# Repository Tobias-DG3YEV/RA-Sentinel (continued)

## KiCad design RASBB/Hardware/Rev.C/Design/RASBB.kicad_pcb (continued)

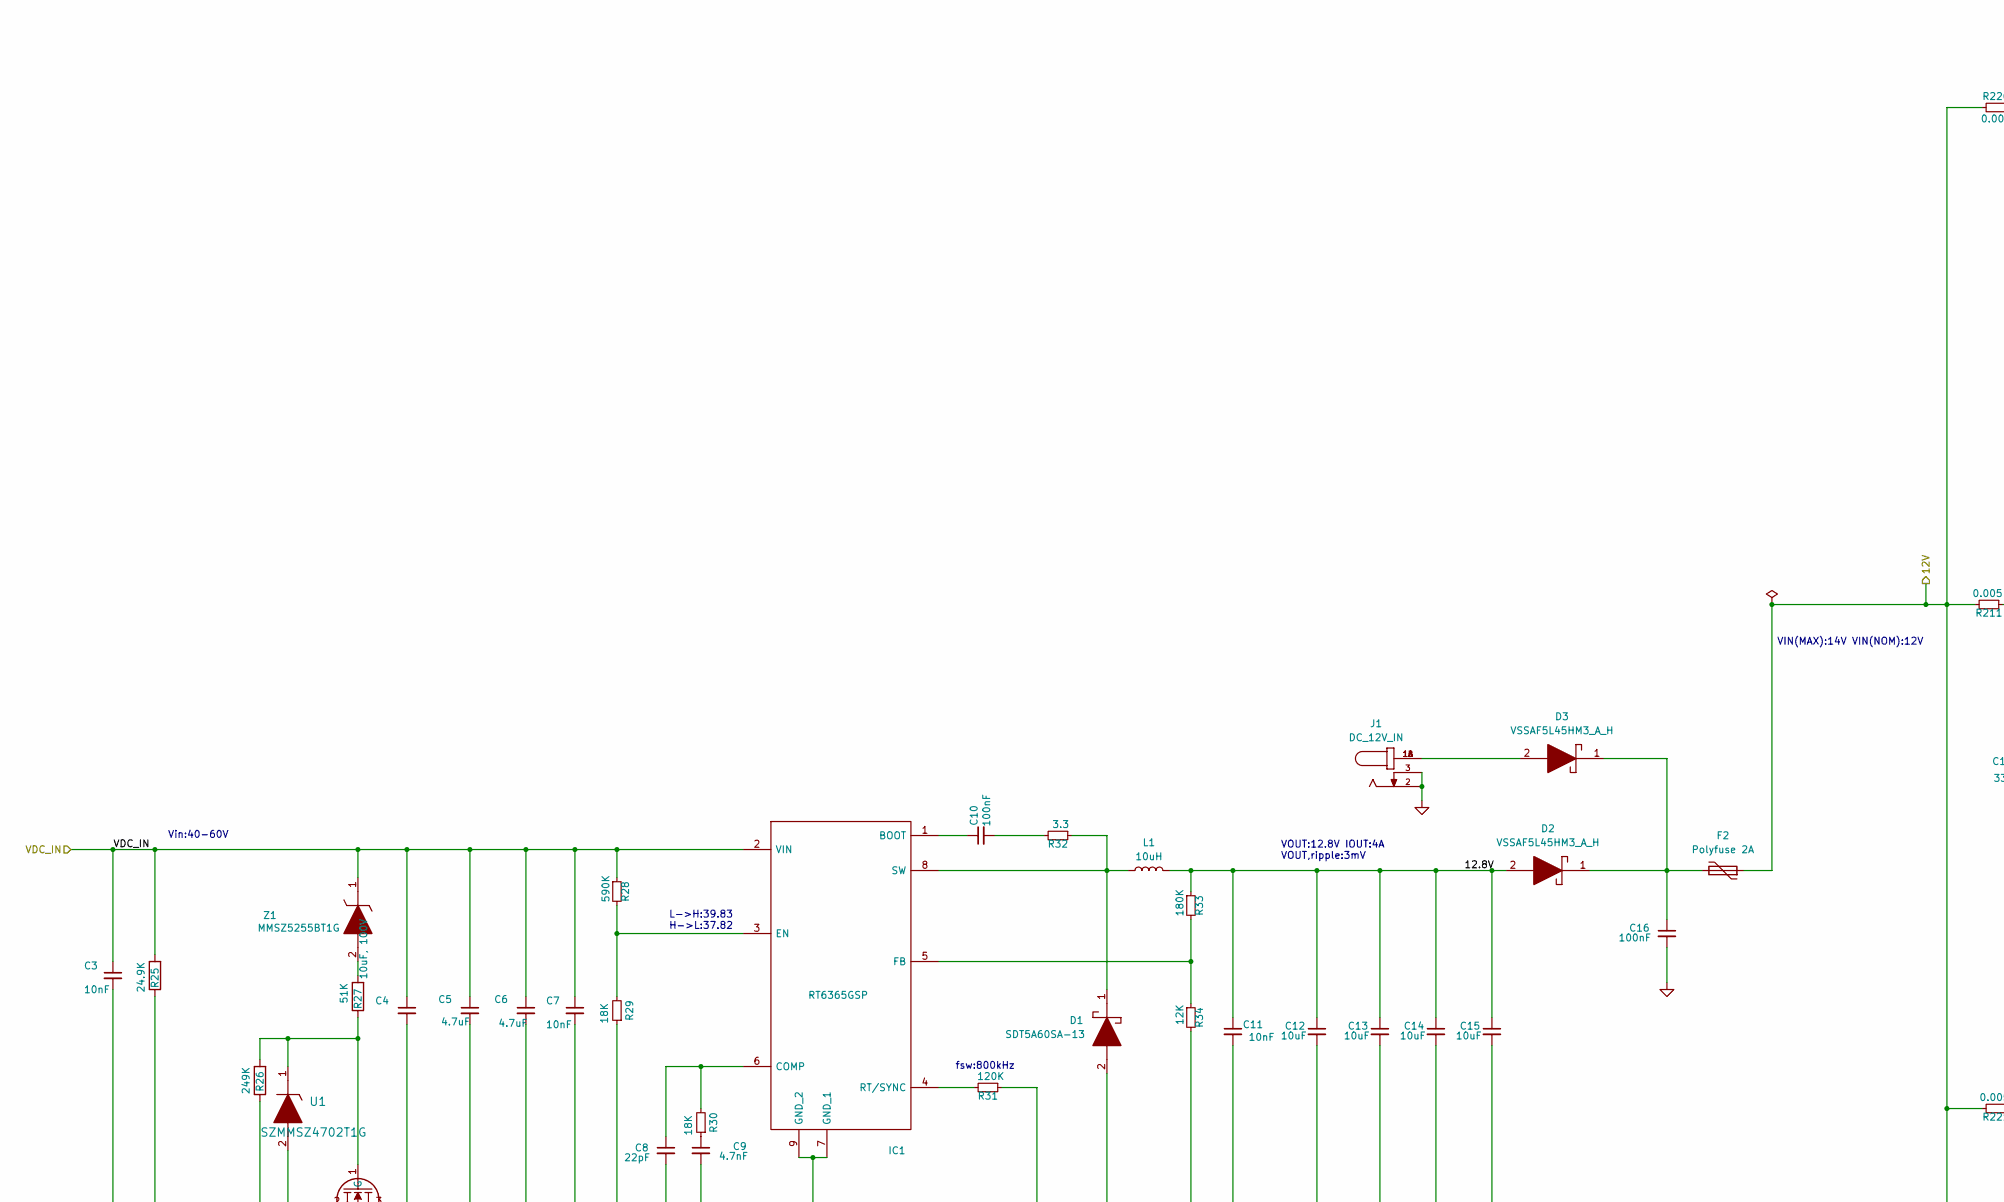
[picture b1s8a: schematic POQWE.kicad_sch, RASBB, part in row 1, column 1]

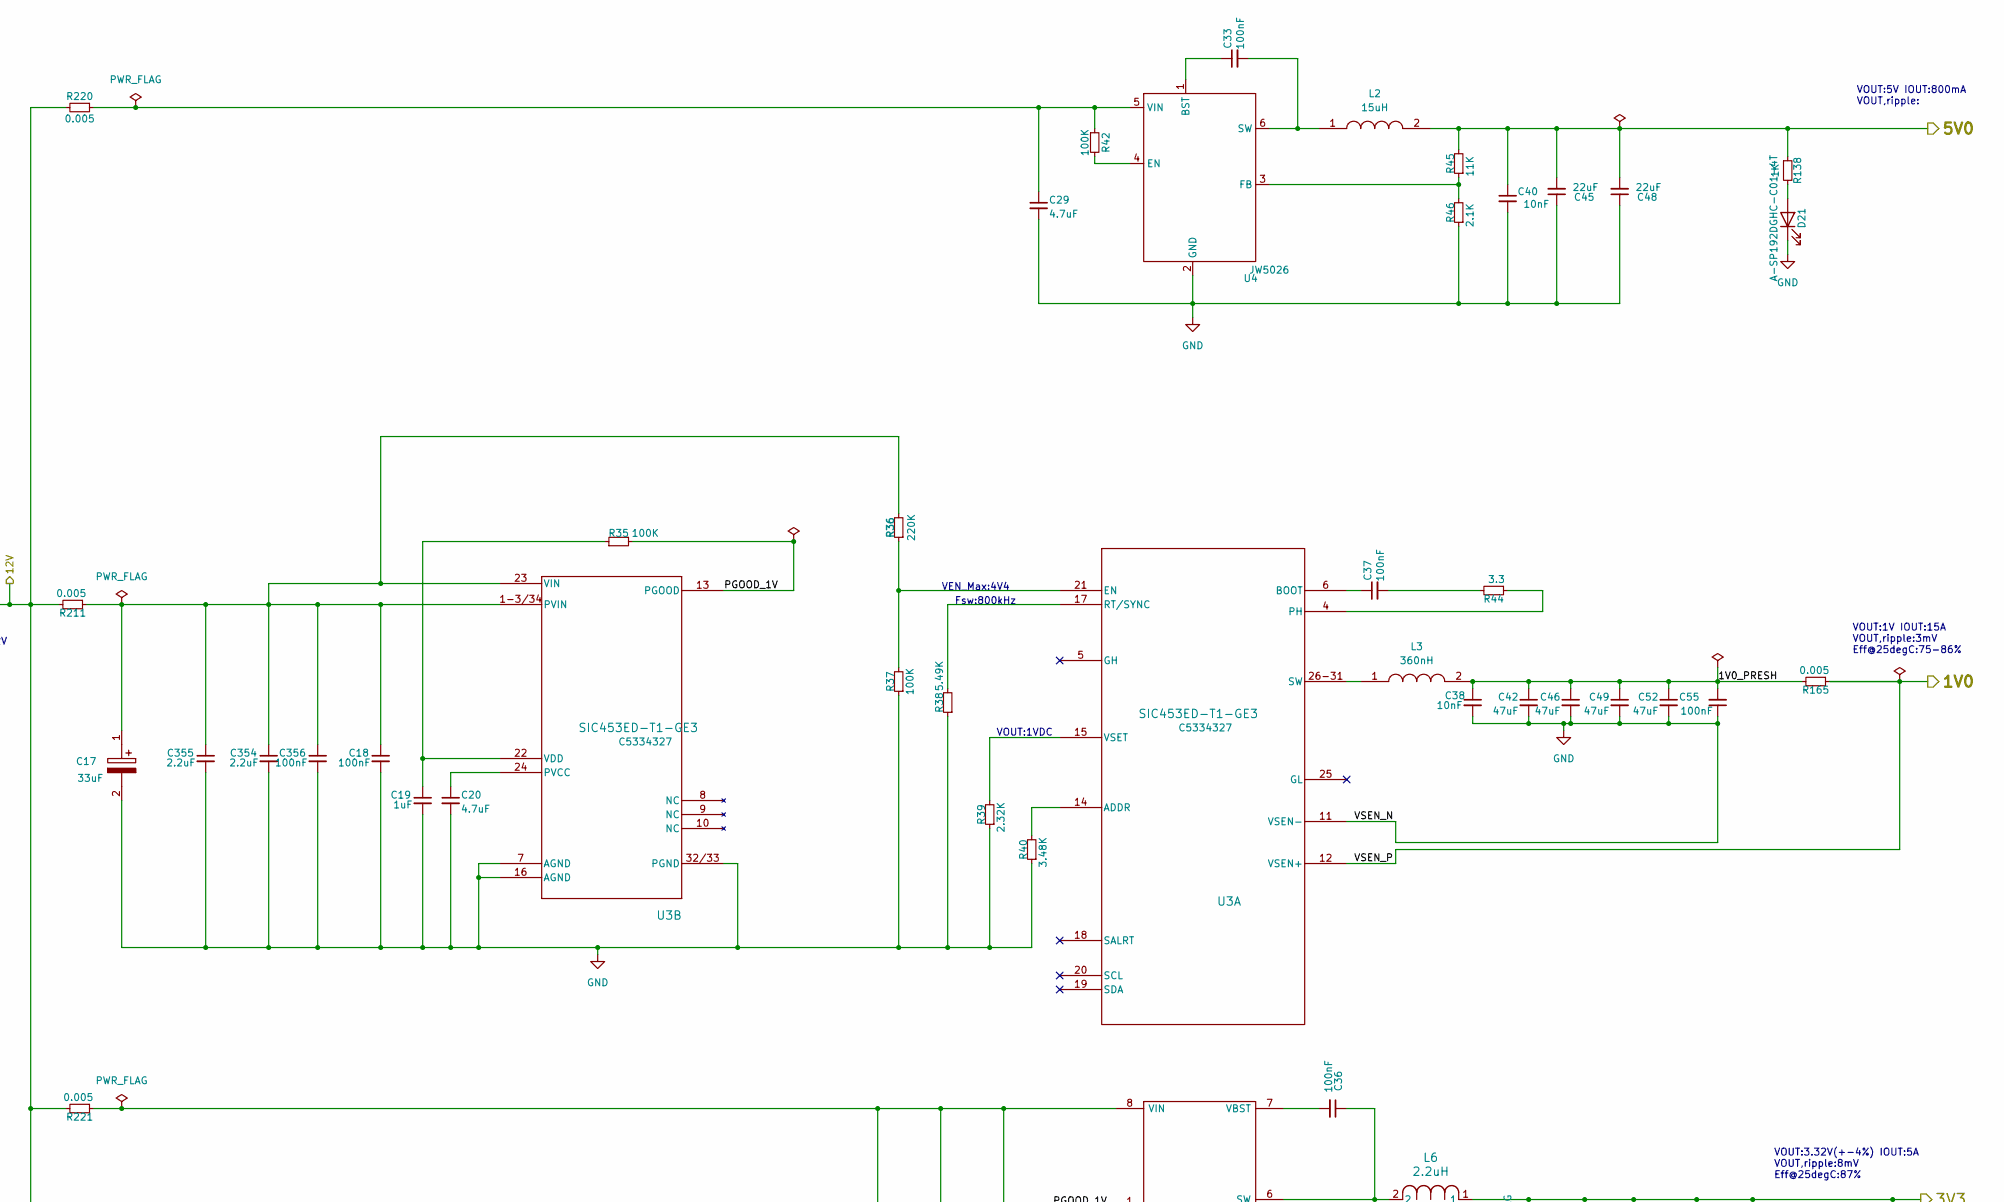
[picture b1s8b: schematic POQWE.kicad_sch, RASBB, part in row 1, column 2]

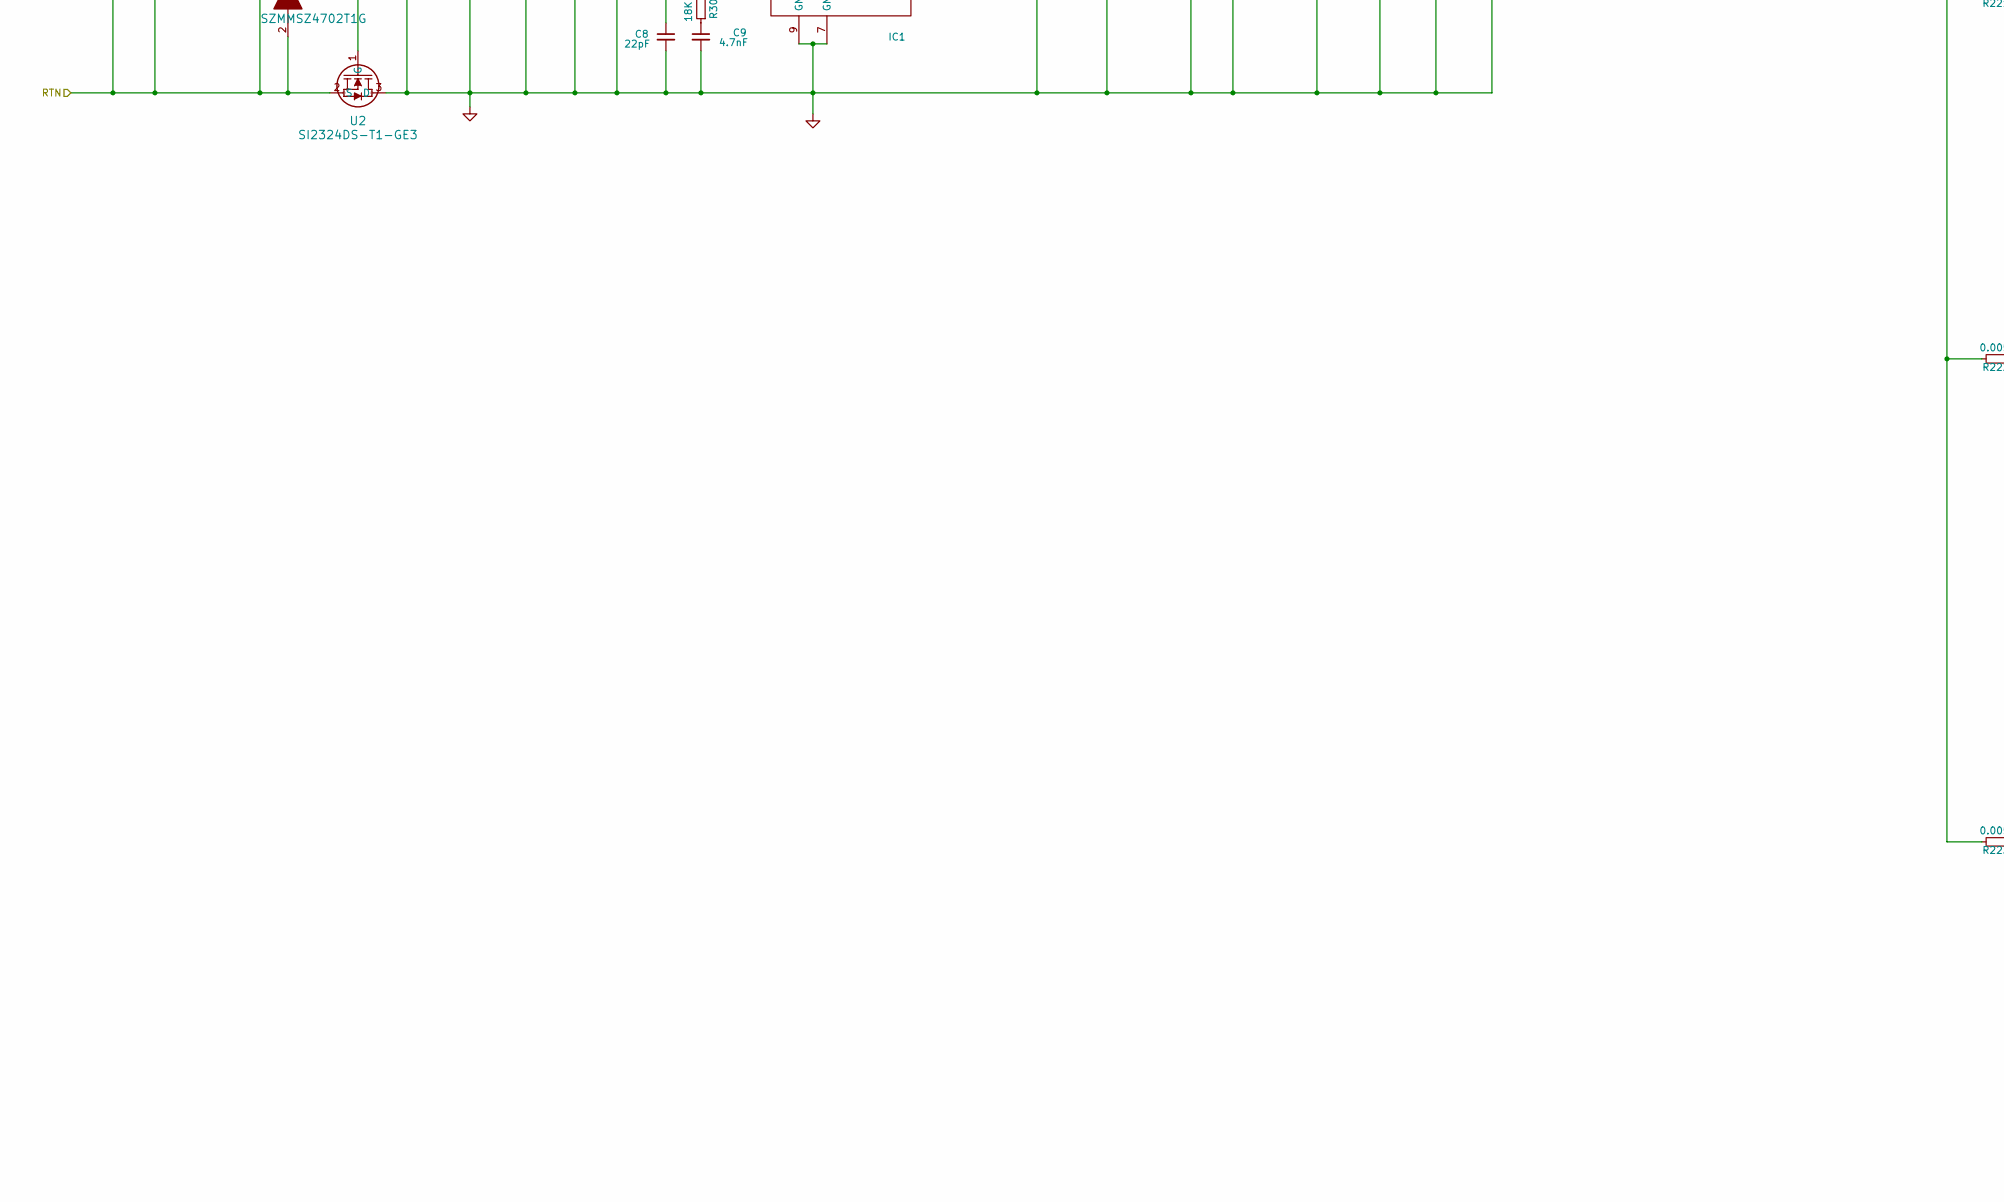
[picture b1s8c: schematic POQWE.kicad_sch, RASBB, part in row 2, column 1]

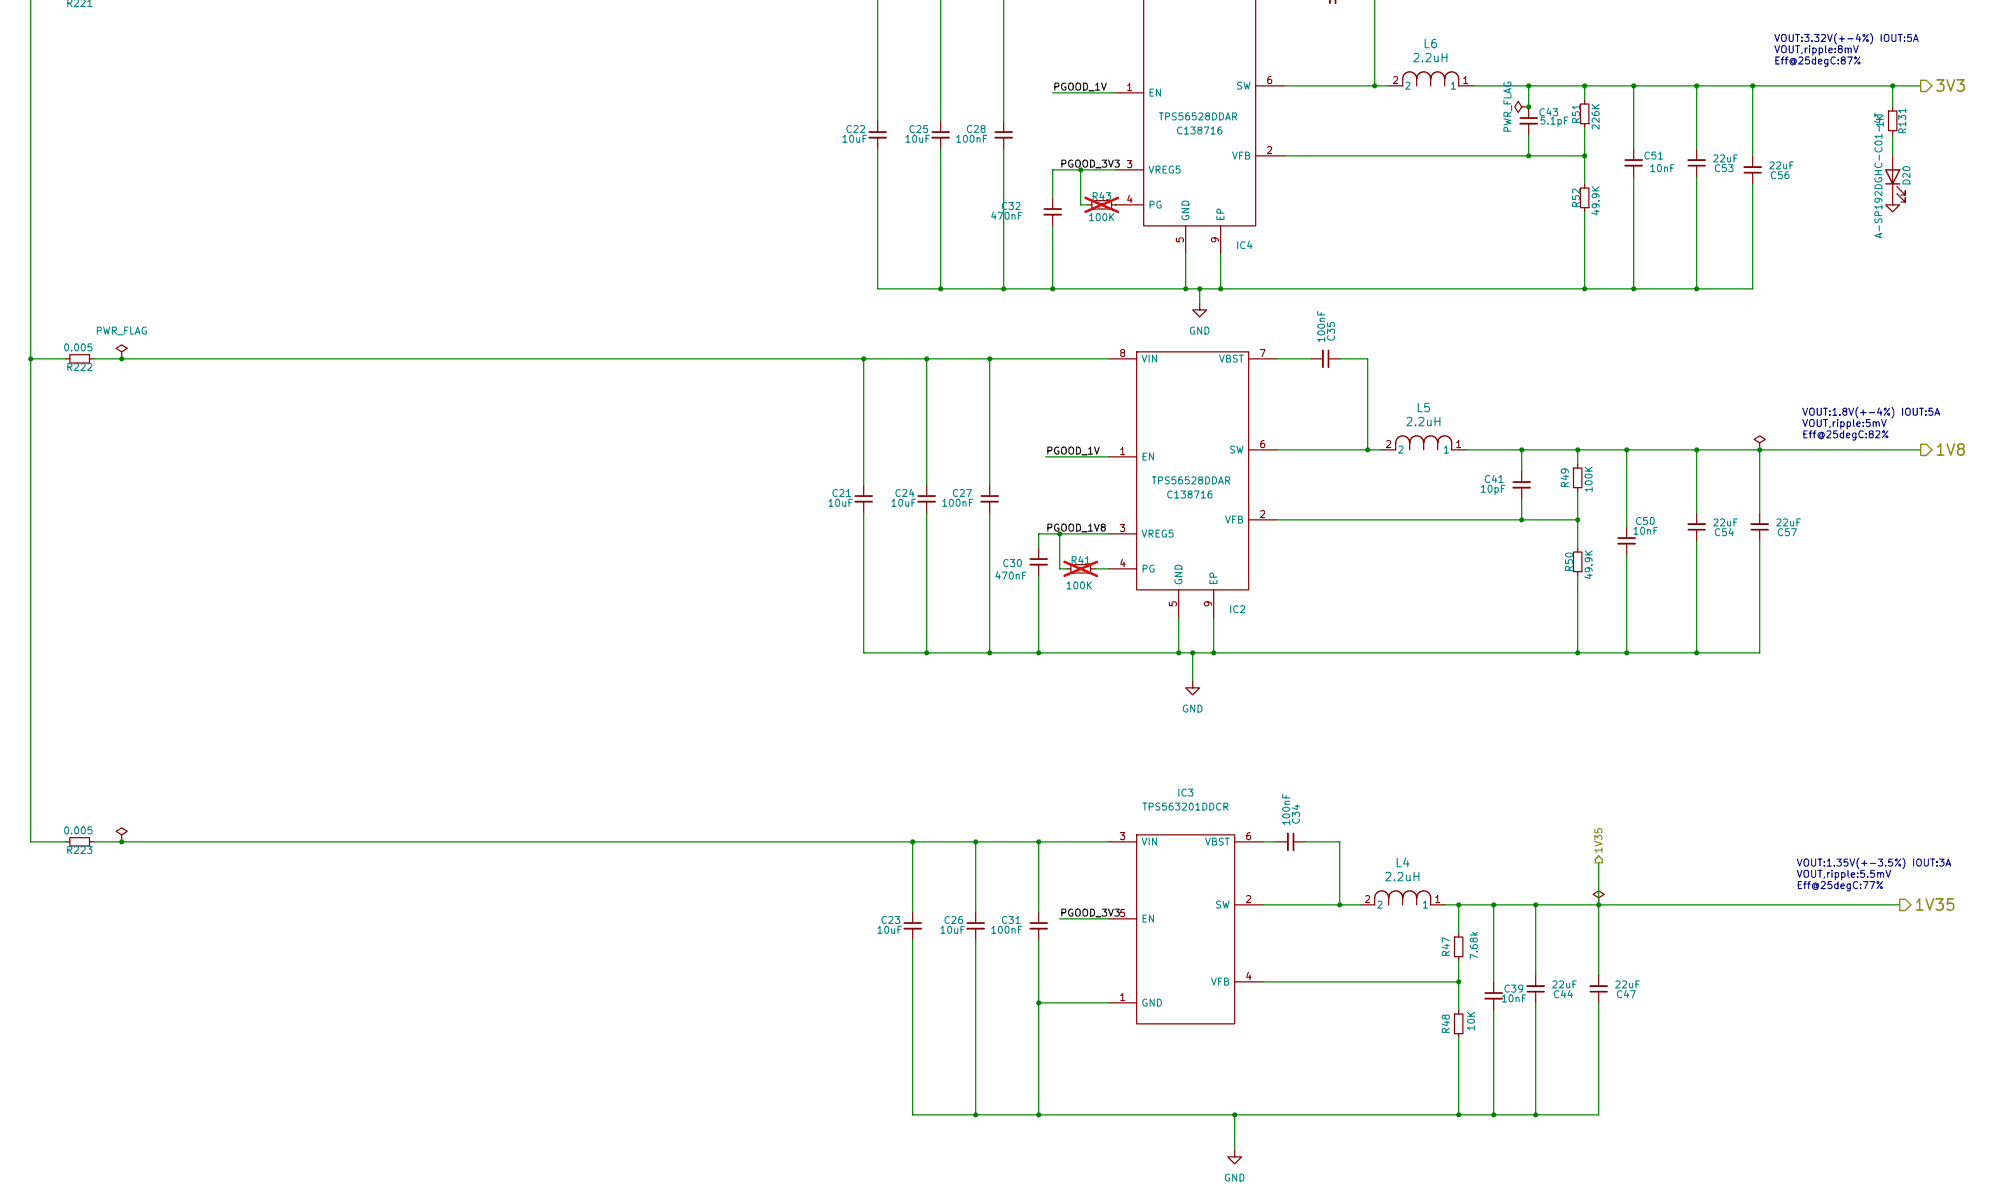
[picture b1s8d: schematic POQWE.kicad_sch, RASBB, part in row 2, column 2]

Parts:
C3, C7: 10nF; C_0603_1608Metric; Mfr. Part # CGA0603X7R103K101JT; LCSC Part # C6119837
C4: 10uF, 100V; C_1206_3216Metric; Mfr. Part # C3216X6S2A106K160AC; LCSC Part # C6872041
C5, C6: 4.7uF; C_1206_3216Metric; Mfr. Part # GRM31CZ72A475KE11L; LCSC Part # C2997285
C8: 22pF; C_0402_1005Metric; Mfr. Part # CC0402JRNPO7BN220; LCSC Part # C2175872
C9: 4.7nF; C_0402_1005Metric; Mfr. Part # CC0402KRX7R6BB472; LCSC Part # C1852867
C10, C16, C18, C27, C28, C31, C33, C34, C35, C36, C37, C55, C356: 100nF; C_0402_1005Metric; Mfr. Part # 0402B104K500CT; LCSC Part # C152814
C11, C38, C39, C40, C50, C51: 10nF; C_0402_1005Metric; Mfr. Part # 0402B103K500CT; LCSC Part # C301927
C12, C13, C14, C15, C21, C22, C23, C24, C25, C26: 10uF; C_1206_3216Metric; Mfr. Part # CGA5L1X7R1H106KT0Y0N; LCSC Part # C531431
C17: 33uF; EEE0JA152UAP; Mfr. Part # EEE-FP1V330AP; LCSC Part # C178581
C19: 1uF; C_0402_1005Metric; Mfr. Part # 0402X105M160CT; LCSC Part # C3889771
C20: 4.7uF; C_0402_1005Metric; Mfr. Part # GRM155R61A475KEAAD; LCSC Part # C77004
C29: 4.7uF; C_0603_1608Metric; Mfr. Part # GMK107BBJ475KA-T; LCSC Part # C7281848
C30, C32: 470nF; C_0402_1005Metric; Mfr. Part # GRM155R71C474KE01D; LCSC Part # C471404
C41: 10pF; C_0402_1005Metric; Mfr. Part # C0402C100J4GAC7867; LCSC Part # C2182752
C42, C46, C49, C52: 47uF; C_0805_2012Metric; Mfr. Part # GRM21BR61A476ME15L; LCSC Part # C124129
C43: 5.1pF; C_0402_1005Metric; Mfr. Part # GRM1555C1E5R1CA01D; LCSC Part # C3855079
C44, C45, C47, C48, C53, C54, C56, C57: 22uF; C_0603_1608Metric; Mfr. Part # 0603YD226MAT2A; LCSC Part # C6776252
C354, C355: 2.2uF; C_0805_2012Metric; Mfr. Part # 0805B225K500CT; LCSC Part # C2918681
D1: SDT5A60SA-13; SDT5A60SA13; Mfr. Part # SDT5A60SA-13; LCSC Part # C3024223
D2, D3: VSSAF5L45HM3_A_H; SODFL5226X100N; Mfr. Part # VSSAF5L45HM3_A/H; LCSC Part # C6000165
D20, D21: A-SP192DGHC-C01-4T; LED_0603_1608Metric; Mfr. Part # A-SP192DGHC-C01-4T; LCSC Part # C19171301
F2: Polyfuse 2A; BSMD1812; Mfr. Part # BSMD1812-200-30V; LCSC Part # C960026
IC1: RT6365GSP; SOIC127P600X175-9N; Mfr. Part # RT6365GSP; LCSC Part # C3024482
IC2, IC4: TPS56528DDAR; SOIC127P600X170-9N; Mfr. Part # TPS56528DDAR; LCSC Part # C138716
IC3: TPS563201DDCR; SOT95P280X110-6N; Mfr. Part # TPS563201DDCR; LCSC Part # C116592
J1: DC_12V_IN; CUI_PJ-002AH-SMT-TR; Mfr. Part # PJ-002AH-SMT-TR; LCSC Part # C22434687
L1: 10uH; 0630CDMCDDS-100MC; Mfr. Part # 0630CDMCDDS-100MC; LCSC Part # C2595948
L2: 15uH; SMDRS6028-150N; Mfr. Part # SMDRS6028-150N; LCSC Part # C163563
L3: 360nH; INDPM109103X400N; Mfr. Part # IHLP4040DZERR36M01; LCSC Part # C845083
L4, L5, L6: 2.2uH; IND_IHLP-2525CZ_VIS; Mfr. Part # IHLP2525EZER2R2M01; LCSC Part # C845037
R25: 24.9K; R_1206_3216Metric; Mfr. Part # WR12X2492FTL; LCSC Part # C171074
R26: 249K; R_0805_2012Metric; Mfr. Part # WR08X2493FTL; LCSC Part # C170853
R27: 51K; R_0603_1608Metric; Mfr. Part # WR06X5102FTL; LCSC Part # C163933
R28: 590K; R_0402_1005Metric; Mfr. Part # WR04X5903FTL; LCSC Part # C172103
R29, R30: 18K; R_0402_1005Metric; Mfr. Part # WR04X1802FTL; LCSC Part # C168206
R31: 120K; R_0402_1005Metric; Mfr. Part # RC0402JR-07120KL; LCSC Part # C137924
R32, R44: 3.3; R_0402_1005Metric; Mfr. Part # CRCW04023R30FKEDC; LCSC Part # C4170964
R33: 180K; R_0402_1005Metric; Mfr. Part # WR04X1803FTL; LCSC Part # C168207
R34: 12K; R_0402_1005Metric; Mfr. Part # SR04X1202FTL; LCSC Part # C2991361
R35, R37, R42, R49: 100K; R_0402_1005Metric; Mfr. Part # RC0402FR-07100KL; LCSC Part # C60491
R36: 220K; R_0402_1005Metric; Mfr. Part # 0402WGF2203TCE; LCSC Part # C25767
R38: 5.49K; R_0402_1005Metric; Mfr. Part # CRCW04025K49FKED; LCSC Part # C2092200
R39: 2.32K; R_0402_1005Metric; Mfr. Part # CRCW04022K32FKED; LCSC Part # C2091739
R40: 3.48K; R_0402_1005Metric; Mfr. Part # CRCW04023K48FKED; LCSC Part # C4336043
R41, R43: 100K; R_0402_1005Metric; Mfr. Part # RC0402FR-07100KL; LCSC Part # C60491; not fitted
R45: 11K; R_0402_1005Metric; Mfr. Part # WR04X113JTL; LCSC Part # C172152
R46: 2.1K; R_0402_1005Metric; Mfr. Part # WR04X2101FTL; LCSC Part # C170256
R47: 7.68k; R_0402_1005Metric; Mfr. Part # WR04X7681FTL; LCSC Part # C334733
R48: 10K; R_0402_1005Metric; Mfr. Part # WR04X1002FTL; LCSC Part # C163810
R50, R52: 49.9K; R_0402_1005Metric; Mfr. Part # CRCW040249K9FKED; LCSC Part # C350874
R51: 226K; R_0402_1005Metric; Mfr. Part # CRCW0402226KFKED; LCSC Part # C2076623
R131, R138: 1K; R_0402_1005Metric; Mfr. Part # MR04X1001FTL; LCSC Part # C327796
R165: 0.005; R_2512_6332Metric; Mfr. Part # FRM252WJR005TN; LCSC Part # C7467241
R211, R220, R221, R222, R223: 0.005; R_2512_6332Metric; Mfr. Part # FRM252WJR005TN; LCSC Part # C7419996
U1: SZMMSZ4702T1G; SOD-123_ONS; Mfr. Part # SZMMSZ4702T1G; LCSC Part # C463904
U2: SI2324DS-T1-GE3; SOT_4DS-T1-GE3_VIS; Mfr. Part # SI2324DS-T1-GE3; LCSC Part # C190351
U3: SIC453ED-T1-GE3; POWERPAK_MLP34-57_VIS; Mfr. Part # SIC453ED-T1-GE3; LCSC Part # C5334327
U4: JW5026; SOT-23-6; Mfr. Part # JW5026; LCSC Part # C185109
Z1: MMSZ5255BT1G; SOD3716X135N; Mfr. Part # MMSZ5255BT1G; LCSC Part # C242284

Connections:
/Audio_IN-OUT/3V3: C43.1, C51.1, C53.2, C56.2, L6.1, R51.2, R131.1; also elsewhere on the board
/Audio_IN-OUT/5V0: C40.1, C45.2, C48.2, L2.2, R45.2, R138.1; also elsewhere on the board
/DDR3-01/VCCO_DDR3: C39.1, C44.2, C47.2, L4.1, R47.1; also elsewhere on the board
/FPGA-01/1V8: C41.1, C50.1, C54.2, C57.2, L5.1, R49.1; also elsewhere on the board
/PCIE/12V: F2.1, R211.2, R220.2, R221.2, R222.2, R223.2; also elsewhere on the board
/POWER/1V0_PRESH: C38.1, C42.1, C46.1, C49.1, C52.1, C55.2, L3.2, R165.2
/POWER/12.8V: C11.1, C12.1, C13.1, C14.1, C15.1, D2.2, L1.2, R33.1
/POWER/PGOOD_1V: IC2.1 (EN), IC4.1 (EN), R35.2, U3.13 (PGOOD)
/POWER/PGOOD_1V8: C30.1, IC2.3 (VREG5), R41.1
/POWER/PGOOD_3V3: C32.1, IC3.5 (EN), IC4.3 (VREG5), R43.1
/POWER/VSEN_P: R165.1, U3.12 (VSEN+); also elsewhere on the board
/VDC_IN: C3.1, C4.1, C5.1, C6.1, C7.1, IC1.2 (VIN), R25.2, R28.1, Z1.1; also elsewhere on the board
/VSS_POE: C3.2, R25.1, R26.1, U1.2, U2.2 (S); also elsewhere on the board
GND: C4.2, C5.2, C6.2, C7.2, C8.2, C9.2, C11.2, C12.2, C13.2, C14.2, C15.2, C16.2, C17.2, C18.2, C19.2, C20.2, C21.2, C22.2, C23.2, C24.2, C25.2, C26.2, C27.2, C28.2, C29.2, C30.2, C31.2, C32.2, C38.2, C39.2, C40.2, C42.2, C44.1, C45.1, C46.2, C47.1, C48.1, C49.2, C50.2, C51.2, C52.2, C53.1, C54.1, C55.1, C56.1, C57.1, C354.2, C355.2, C356.2, D1.2, D20.1 (K), D21.1 (K), IC1.7 (GND_1), IC1.9 (GND_2), IC2.5 (GND), IC2.9 (EP), IC3.1 (GND), IC4.5 (GND), IC4.9 (EP), J1.2, J1.3, R29.1, R31.1, R34.2, R37.1, R38.1, R39.1, R40.1, R46.1, R48.2, R50.1, R52.1, U2.3 (D), U3.7 (AGND), U3.11 (VSEN-), U3.16 (AGND), U3.32/33 (PGND), U4.2 (GND); also elsewhere on the board
unnamed: C9.1, R30.1
unnamed: C10.2, R32.2
unnamed: C16.1, D2.1, D3.1, F2.2
unnamed: C37.2, R44.2
unnamed: D3.2, J1.1A, J1.1B
unnamed: D20.2 (A), R131.2
unnamed: D21.2 (A), R138.2
unnamed: C10.1, IC1.1 (BOOT)
unnamed: C8.1, IC1.6 (COMP), R30.2
unnamed: IC1.3 (EN), R28.2, R29.2
unnamed: IC1.5 (FB), R33.2, R34.1
unnamed: IC1.4 (RT/SYNC), R31.2
unnamed: D1.1, IC1.8 (SW), L1.1, R32.1
unnamed: IC2.4 (PG), R41.2
unnamed: C35.1, IC2.6 (SW), L5.2
unnamed: C35.2, IC2.7 (VBST)
unnamed: C41.2, IC2.2 (VFB), R49.2, R50.2
unnamed: C21.1, C24.1, C27.1, IC2.8 (VIN), R222.1
unnamed: C34.1, IC3.2 (SW), L4.2
unnamed: C34.2, IC3.6 (VBST)
unnamed: IC3.4 (VFB), R47.2, R48.1
unnamed: C23.1, C26.1, C31.1, IC3.3 (VIN), R223.1
unnamed: IC4.4 (PG), R43.2
unnamed: C36.1, IC4.6 (SW), L6.2
unnamed: C36.2, IC4.7 (VBST)
unnamed: C43.2, IC4.2 (VFB), R51.1, R52.2
unnamed: C22.1, C25.1, C28.1, IC4.8 (VIN), R221.1
unnamed: R27.2, Z1.2
unnamed: R26.2, R27.1, U1.1, U2.1 (G)
unnamed: R40.2, U3.14 (ADDR)
unnamed: C37.1, U3.6 (BOOT)
unnamed: R36.1, R37.2, U3.21 (EN)
unnamed: R44.1, U3.4 (PH)
unnamed: R38.2, U3.17 (RT/SYNC)
unnamed: L3.1, U3.26-31 (SW)
unnamed: R39.2, U3.15 (VSET)
unnamed: C20.1, U3.24 (PVCC)
unnamed: C17.1, C18.1, C354.1, C355.1, C356.1, R36.2, R211.1, U3.1-3/34 (PVIN), U3.23 (VIN)
unnamed: C19.1, R35.1, U3.22 (VDD)
unnamed: C33.1, U4.1 (BST)
unnamed: R42.2, U4.4 (EN)
unnamed: R45.1, R46.2, U4.3 (FB)
unnamed: C33.2, L2.1, U4.6 (SW)
unnamed: C29.1, R42.1, R220.1, U4.5 (VIN)

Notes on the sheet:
Fsw:800kHz
L->H:39.83 H->L:37.82
VIN(MAX):14V VIN(NOM):12V
VOUT:1.8V(+-4%) IOUT:5A VOUT,ripple:5mV Eff@25degC:82%
VOUT:12.8V IOUT:4A VOUT,ripple:3mV
VOUT:3.32V(+-4%) IOUT:5A VOUT,ripple:8mV Eff@25degC:87%
VOUT:5V IOUT:800mA VOUT,ripple:
VOUT:1VDC
Vin:40-60V
VOUT:1.35V(+-3.5%) IOUT:3A VOUT,ripple:5.5mV Eff@25degC:77%
fsw:800kHz
VEN_Max:4V4
VOUT:1V IOUT:15A VOUT,ripple:3mV Eff@25degC:75-86%

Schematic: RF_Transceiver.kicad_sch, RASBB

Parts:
C145, C149: 20p; C_0402_1005Metric; Mfr. Part # 0402N200J500CT; LCSC Part # C123468
C146, C147: 10uF; C_0402_1005Metric; Mfr. Part # 0402X106M100CT; LCSC Part # C2992625
C148, C152, C154: 100nF; C_0402_1005Metric; Mfr. Part # 0402B104K500CT; LCSC Part # C152814
C150, C151: 10nF; C_0402_1005Metric; Mfr. Part # 0402B103K500CT; LCSC Part # C301927
C153: 470nF; C_0402_1005Metric; Mfr. Part # GRM155R71C474KE01D; LCSC Part # C471404
C155: 0.8pF; C_0402_1005Metric; Mfr. Part # RF15N0R8B500CT; LCSC Part # C396870
C156, C158: 1.2pF; C_0402_1005Metric; Mfr. Part # 0402N1R2C500CT; LCSC Part # C301969
C157: 0.5pF; C_0402_1005Metric; Mfr. Part # RT15N0R5B500CT; LCSC Part # C2918554
C159: 100pF; C_0402_1005Metric; Mfr. Part # 0402N101G500CT; LCSC Part # C387967
FB3: BLM15BD601SH1D; NFZ15SG152SN10B; Mfr. Part # BLM15BD601SH1D; LCSC Part # C710334
IC13: SX1280IMLTRT; QFN50P400X400X100-25N-D; Mfr. Part # SX1280IMLTRT; LCSC Part # C125969
J11: LORA_ANT; U.FL_Hirose_U.FL-R-SMT-1_Vertical; Mfr. Part # CONUFL001-SMD-T or similar; LCSC Part # C22418213
L9: 3nH; L_0402_1005Metric; Mfr. Part # MHQ1005P3N0BT000; LCSC Part # C433005
L10: 2.5nH; L_0402_1005Metric; Mfr. Part # FHW0402UC2N5KST; LCSC Part # C317668
Y2: XC21M4-52.000-F10NNHPL; Mfr. Part # XC21M4-52.000-F10NNHPL; LCSC Part # C3034316

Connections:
/Audio_IN-OUT/3V3: FB3.1; also elsewhere on the board
/RF_Transceiver/BUSY_LORA_G: IC13.7 (BUSY); also elsewhere on the board
/RF_Transceiver/DIO1_LORA_G: IC13.8 (DIO1); also elsewhere on the board
/RF_Transceiver/DIO2_LORA_G: IC13.9 (DIO2); also elsewhere on the board
/RF_Transceiver/DIO3_LORA_G: IC13.10 (DIO3); also elsewhere on the board
/RF_Transceiver/LORA_VDDIO: C146.1, C147.1, C148.1, C152.1, C154.1, FB3.2, IC13.11 (VBAT_IO), IC13.15 (VBAT)
/RF_Transceiver/NRST_LORA_G: IC13.3 (NRESET); also elsewhere on the board
/RF_Transceiver/SPI_MISO_LORA_G: IC13.16 (MISO_TX); also elsewhere on the board
/RF_Transceiver/SPI_MOSI_LORA_G: IC13.17 (MOSI_RX); also elsewhere on the board
/RF_Transceiver/SPI_NSS_LORA_G: IC13.19 (NSS_CTS); also elsewhere on the board
/RF_Transceiver/SPI_SCK_LORA_G: IC13.18 (SCK_RTSN); also elsewhere on the board
GND: C145.2, C146.2, C147.2, C148.2, C149.2, C150.2, C151.2, C152.2, C153.2, C154.2, C155.2, C156.2, C158.2, IC13.5 (GND_1), IC13.13 (GND_2), IC13.20 (GND_3), IC13.21 (GND_4), IC13.23 (GND_5), IC13.24 (GND_6), IC13.25 (EP), J11.2 (Ext), Y2.2 (GND_1), Y2.4 (GND_2); also elsewhere on the board
unnamed: C156.1, C157.1, L9.2, L10.1
unnamed: C157.2, C158.1, C159.2, L10.2
unnamed: C150.1, C153.1, IC13.2 (VDD_IN), IC13.12 (DCC_FB)
unnamed: C155.1, IC13.22 (RFIO), L9.1
unnamed: C151.1, IC13.1 (VR_PA)
unnamed: C149.1, IC13.4 (XTA), Y2.3 (XTAL_2)
unnamed: C145.1, IC13.6 (XTB), Y2.1 (XTAL_1)
unnamed: C159.1, J11.1 (In)

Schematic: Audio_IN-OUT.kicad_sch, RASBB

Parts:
C160, C161, C166: 10uF; C_0603_1608Metric; Mfr. Part # 0603X106M250CT; LCSC Part # C4555498
C162: 47nF; C_0402_1005Metric; Mfr. Part # C0402C473J8RAC7867; LCSC Part # C2178375
C163: 100pF; C_0402_1005Metric; Mfr. Part # 0402N101G500CT; LCSC Part # C387967
C164, C353: 100nF; C_0402_1005Metric; Mfr. Part # 0402B104K500CT; LCSC Part # C152814
C165: UUD1A221MCL1GS; CAPAE660X800N; Mfr. Part # UUD1A221MCL1GS; LCSC Part # C445275
C167: 1uF; C_0402_1005Metric; Mfr. Part # 0402X105M160CT; LCSC Part # C3889771
J12: AUDIO; FC68128; Mfr. Part # HC-PJ-313E8-B-SMT; LCSC Part # C7501803
R67, R124: 10K; R_0402_1005Metric; Mfr. Part # WR04X1002FTL; LCSC Part # C163810
R121: 1.2K; R_0402_1005Metric; Mfr. Part # WR04X1201FTL; LCSC Part # C168197
R122: 10; R_0402_1005Metric; Mfr. Part # 0402WGF100JTCE; LCSC Part # C25077
R123: 51K; R_0603_1608Metric; Mfr. Part # WR06X5102FTL; LCSC Part # C163933
R125, R126: 100K; R_0402_1005Metric; Mfr. Part # RC0402FR-07100KL; LCSC Part # C60491
R127: 5.6K; R_0402_1005Metric; Mfr. Part # WR04X5601FTL; LCSC Part # C168239
U8: LM386; SOP-8_3.9x4.9mm_P1.27mm; Mfr. Part # LM386D; LCSC Part # C510560
U9: LM321; SOT-23-5; Mfr. Part # LM321-TR; LCSC Part # C280706

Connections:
/Audio_IN-OUT/3V3: C164.1, R67.2, R125.2, R127.1, U9.5 (V+); also elsewhere on the board
/Audio_IN-OUT/5V0: C353.1, U8.6 (V+); also elsewhere on the board
/Audio_IN-OUT/Audio_IN: C163.2, R123.2, U9.4; also elsewhere on the board
/Audio_IN-OUT/Audio_PTT: J12.4A (R1), J12.4B (R1), R67.1; also elsewhere on the board
/Audio_IN-OUT/LM386_INP: U8.3 (+); also elsewhere on the board
GND: C160.2, C162.2, C164.2, C353.2, J12.1A (S), J12.1B (S), R124.2, R126.1, U8.2 (-), U8.4 (GND), U9.2 (V-); also elsewhere on the board
unnamed: C161.1, U8.8 (GAIN)
unnamed: C161.2, R121.2
unnamed: C162.1, R122.1
unnamed: C165.1, R122.2, U8.5
unnamed: C165.2, J12.2A (T), J12.2B (T)
unnamed: C166.2, R124.1
unnamed: C167.2, J12.3A (R2), J12.3B (R2), R127.2
unnamed: R121.1, U8.1 (GAIN)
unnamed: C160.1, U8.7 (BYPASS)
unnamed: C167.1, R125.1, R126.2, U9.1 (+)
unnamed: C163.1, C166.1, R123.1, U9.3 (-)

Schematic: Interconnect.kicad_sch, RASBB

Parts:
C125, C256: 22uF; C_0603_1608Metric; Mfr. Part # 0603YD226MAT2A; LCSC Part # C6776252
J5: ICON; CON50_1X50_DUTB_HRS_HIR; Mfr. Part # FH12-50S-0.5SVA(54); LCSC Part # C597991
RN1, RN2, RN3, RN4, RN5, RN6, RN7, RN8, RN9, RN10: CAY10-330J4LF; CAY10-XXXJ4; Mouser Part Number 652-CAY10-330J4LF

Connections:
/Audio_IN-OUT/3V3: C125.2, C256.2, J5.1, J5.41; also elsewhere on the board
/DEBUG_A0_F: RN1.5; also elsewhere on the board
/DEBUG_A1_F: RN5.4; also elsewhere on the board
/DEBUG_A2_F: RN1.6; also elsewhere on the board
/DEBUG_A3_F: RN5.3; also elsewhere on the board
/DEBUG_A4_F: RN1.7; also elsewhere on the board
/DEBUG_A5_F: RN5.2; also elsewhere on the board
/DEBUG_A6_F: RN1.8; also elsewhere on the board
/DEBUG_A7_F: RN5.1; also elsewhere on the board
/DEBUG_D0_F: RN2.5; also elsewhere on the board
/DEBUG_D1_F: RN6.4; also elsewhere on the board
/DEBUG_D2_F: RN2.6; also elsewhere on the board
/DEBUG_D3_F: RN6.3; also elsewhere on the board
/DEBUG_D4_F: RN2.7; also elsewhere on the board
/DEBUG_D5_F: RN6.2; also elsewhere on the board
/DEBUG_D6_F: RN2.8; also elsewhere on the board
/DEBUG_D7_F: RN6.1; also elsewhere on the board
/DEBUG_D8_F: RN3.5; also elsewhere on the board
/DEBUG_D9_F: RN7.4; also elsewhere on the board
/DEBUG_D10_F: RN3.6; also elsewhere on the board
/DEBUG_D11_F: RN7.3; also elsewhere on the board
/DEBUG_D12_F: RN3.7; also elsewhere on the board
/DEBUG_D13_F: RN7.2; also elsewhere on the board
/DEBUG_D14_F: RN3.8; also elsewhere on the board
/DEBUG_D15_F: RN7.1; also elsewhere on the board
/DEBUG_D16_F: RN4.5; also elsewhere on the board
/DEBUG_D17_F: RN8.4; also elsewhere on the board
/DEBUG_D18_F: RN4.6; also elsewhere on the board
/DEBUG_D19_F: RN8.3; also elsewhere on the board
/DEBUG_D20_F: RN4.7; also elsewhere on the board
/DEBUG_D21_F: RN8.2; also elsewhere on the board
/DEBUG_D22_F: RN4.8; also elsewhere on the board
/DEBUG_D23_F: RN8.1; also elsewhere on the board
/DEBUG_D24_F: RN9.8; also elsewhere on the board
/DEBUG_D25_F: RN10.4; also elsewhere on the board
/DEBUG_D26_F: RN9.7; also elsewhere on the board
/DEBUG_D27_F: RN10.3; also elsewhere on the board
/DEBUG_D28_F: RN9.6; also elsewhere on the board
/DEBUG_D29_F: RN10.2; also elsewhere on the board
/DEBUG_D30_F: RN9.5; also elsewhere on the board
/DEBUG_D31_F: RN10.1; also elsewhere on the board
/Interconnect/Debug_A0: J5.3, RN1.4
/Interconnect/Debug_A1: J5.4, RN5.5
/Interconnect/Debug_A2: J5.5, RN1.3
/Interconnect/Debug_A3: J5.6, RN5.6
/Interconnect/Debug_A4: J5.7, RN1.2
/Interconnect/Debug_A5: J5.8, RN5.7
/Interconnect/Debug_A6: J5.9, RN1.1
/Interconnect/Debug_A7: J5.10, RN5.8
/Interconnect/Debug_D0: J5.13, RN2.4
/Interconnect/Debug_D1: J5.12, RN6.5
/Interconnect/Debug_D2: J5.15, RN2.3
/Interconnect/Debug_D3: J5.14, RN6.6
/Interconnect/Debug_D4: J5.17, RN2.2
/Interconnect/Debug_D5: J5.16, RN6.7
/Interconnect/Debug_D6: J5.19, RN2.1
/Interconnect/Debug_D7: J5.18, RN6.8
/Interconnect/Debug_D8: J5.23, RN3.4
/Interconnect/Debug_D9: J5.22, RN7.5
/Interconnect/Debug_D10: J5.25, RN3.3
/Interconnect/Debug_D11: J5.24, RN7.6
/Interconnect/Debug_D12: J5.27, RN3.2
/Interconnect/Debug_D13: J5.26, RN7.7
/Interconnect/Debug_D14: J5.29, RN3.1
/Interconnect/Debug_D15: J5.28, RN7.8
/Interconnect/Debug_D16: J5.33, RN4.4
/Interconnect/Debug_D17: J5.32, RN8.5
/Interconnect/Debug_D18: J5.35, RN4.3
/Interconnect/Debug_D19: J5.34, RN8.6
/Interconnect/Debug_D20: J5.37, RN4.2
/Interconnect/Debug_D21: J5.36, RN8.7
/Interconnect/Debug_D22: J5.39, RN4.1
/Interconnect/Debug_D23: J5.38, RN8.8
/Interconnect/Debug_D24: J5.43, RN9.4
/Interconnect/Debug_D25: J5.42, RN10.5
/Interconnect/Debug_D26: J5.45, RN9.3
/Interconnect/Debug_D27: J5.44, RN10.6
/Interconnect/Debug_D28: J5.47, RN9.2
/Interconnect/Debug_D29: J5.46, RN10.7
/Interconnect/Debug_D30: J5.49, RN9.1
/Interconnect/Debug_D31: J5.48, RN10.8
GND: C125.1, C256.1, J5.2, J5.11, J5.20, J5.21, J5.30, J5.31, J5.40, J5.50; also elsewhere on the board

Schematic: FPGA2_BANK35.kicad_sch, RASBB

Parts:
C199: 100uF; C_1206_3216Metric; Mfr. Part # GRM31CR61A107MEA8L; LCSC Part # C883598
C342: 100nF; C_0402_1005Metric; Mfr. Part # 0402B104K500CT; LCSC Part # C152814
C346, C347, C348, C349: 470nF; C_0402_1005Metric; Mfr. Part # GRM155R71C474KE01D; LCSC Part # C471404
C350, C351: 4.7uF; C_0402_1005Metric; Mfr. Part # GRM155R61A475KEAAD; LCSC Part # C77004
J18: FPGA2_CLK_OUT; PinHeader_1x02_P2.54mm_Vertical; Mfr. Part # PZ254V-11-02P; LCSC Part # C492401
R72, R166, R167: 49.9; R_0402_1005Metric; Mfr. Part # RMCF0402FT49R9; LCSC Part # C4229190
U11: XC7A100T-CSG324; BGA324C80P18X18_1500X1500X150; Mfr. Part # XC7A100T-2CSG324I; LCSC Part # C1521791
X4: OT2EL4C4JI-111OLP-50M; Oscillator_SMD_Abracon_ASE-4Pin_3.2x2.5mm; Mfr. Part # OT2EL4C4JI-111OLP-50M; LCSC Part # C5203552

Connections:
/Audio_IN-OUT/3V3: C199.1, C346.1, C347.1, C348.1, C349.1, C350.1, C351.1, R72.2, U11.A7 (VCCO_35), U11.C3 (VCCO_35), U11.D6 (VCCO_35), U11.F2 (VCCO_35), U11.G5 (VCCO_35), U11.J1 (VCCO_35); also elsewhere on the board
/Ethernet_FPGA/G_ETH_RESET: U11.A3 (IO_L8N_T1_AD14N_35); also elsewhere on the board
/Ethernet_FPGA/RGMII_MDC: U11.A1 (IO_L9N_T1_DQS_AD7N_35); also elsewhere on the board
/Ethernet_FPGA/RGMII_MDIO: U11.B1 (IO_L9P_T1_DQS_AD7P_35); also elsewhere on the board
/Ethernet_FPGA/RGMII_RXC: U11.E1 (IO_L18N_T2_35); also elsewhere on the board
/Ethernet_FPGA/RGMII_RXD0: U11.C1 (IO_L16N_T2_35); also elsewhere on the board
/Ethernet_FPGA/RGMII_RXD1: U11.C2 (IO_L16P_T2_35); also elsewhere on the board
/Ethernet_FPGA/RGMII_RXD2: U11.D2 (IO_L14N_T2_SRCC_35); also elsewhere on the board
/Ethernet_FPGA/RGMII_RXD3: U11.E2 (IO_L14P_T2_SRCC_35); also elsewhere on the board
/Ethernet_FPGA/RGMII_RXDV: U11.B3 (IO_L10P_T1_AD15P_35); also elsewhere on the board
/Ethernet_FPGA/RGMII_TXC: U11.F4 (IO_L13P_T2_MRCC_35); also elsewhere on the board
/Ethernet_FPGA/RGMII_TXD0: U11.F1 (IO_L18P_T2_35); also elsewhere on the board
/Ethernet_FPGA/RGMII_TXD1: U11.G1 (IO_L17N_T2_35); also elsewhere on the board
/Ethernet_FPGA/RGMII_TXD2: U11.H1 (IO_L17P_T2_35); also elsewhere on the board
/Ethernet_FPGA/RGMII_TXD3: U11.H2 (IO_L15P_T2_DQS_35); also elsewhere on the board
/Ethernet_FPGA/RGMII_TX_EN: U11.G2 (IO_L15N_T2_DQS_35); also elsewhere on the board
/FPGA-02/F2_B35_J2: U11.J2 (IO_L22N_T3_35); also elsewhere on the board
GND: C199.2, C342.2, C346.2, C347.2, C348.2, C349.2, C350.2, C351.2, J18.2, X4.2 (GND); also elsewhere on the board
unnamed: J18.1, R167.1
unnamed: R167.2, U11.D3 (IO_L12N_T1_MRCC_35)
unnamed: R166.2, U11.E3 (IO_L12P_T1_MRCC_35)
unnamed: C342.1, R72.1, X4.1 (EN), X4.4 (Vdd)
unnamed: R166.1, X4.3 (OUT)

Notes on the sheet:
Clock Test Output
